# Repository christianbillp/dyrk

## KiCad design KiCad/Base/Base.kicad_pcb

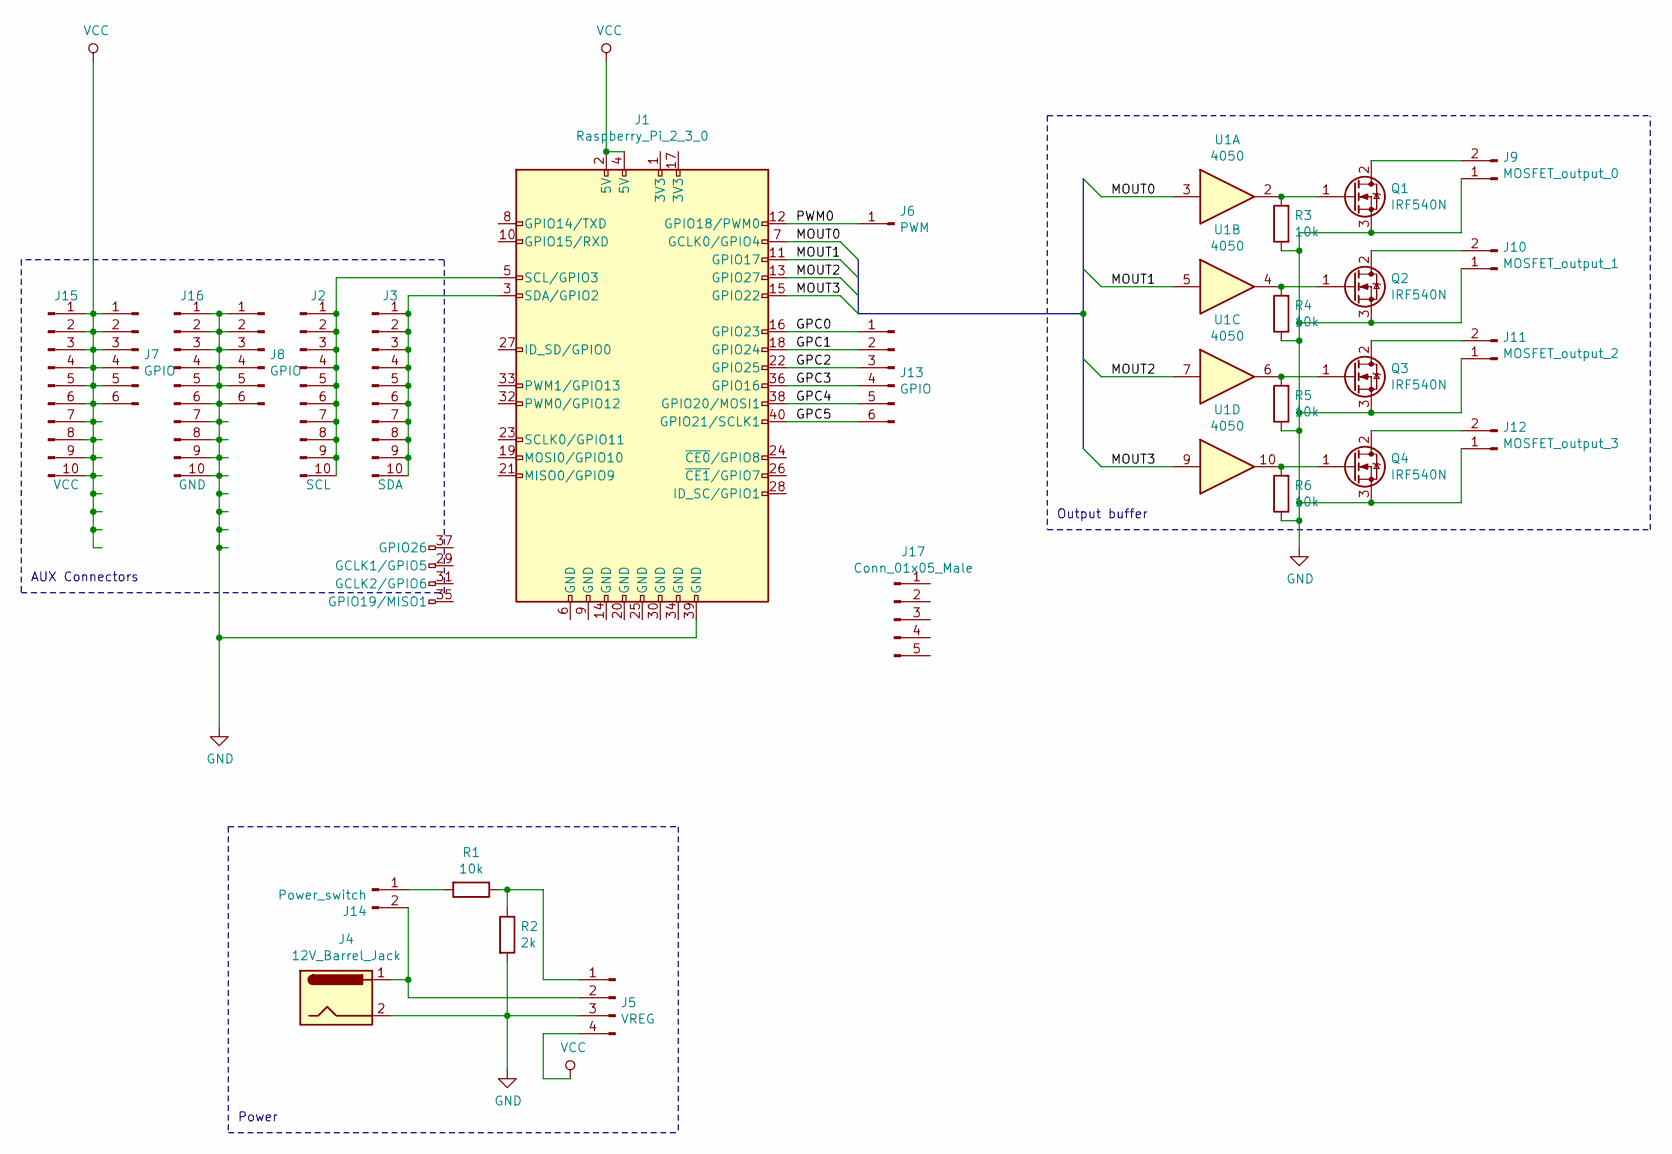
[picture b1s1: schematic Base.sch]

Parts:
J1: Raspberry_Pi_2_3_0; PinHeader_2x20_P2.54mm_Vertical
J2: SCL; PinHeader_1x10_P2.54mm_Vertical
J3: SDA; PinHeader_1x10_P2.54mm_Vertical
J4: 12V_Barrel_Jack; BarrelJack_Horizontal
J5: VREG; PinHeader_1x04_P2.54mm_Vertical
J6: PWM; PinHeader_1x01_P2.54mm_Vertical
J7, J8, J13: GPIO; PinHeader_1x06_P2.54mm_Vertical
J9: MOSFET_output_0; PinHeader_1x02_P2.54mm_Vertical
J10: MOSFET_output_1; PinHeader_1x02_P2.54mm_Vertical
J11: MOSFET_output_2; PinHeader_1x02_P2.54mm_Vertical
J12: MOSFET_output_3; PinHeader_1x02_P2.54mm_Vertical
J14: Power_switch; PinHeader_1x02_P2.54mm_Vertical
J15: VCC; PinHeader_1x10_P2.54mm_Vertical
J16: GND; PinHeader_1x10_P2.54mm_Vertical
J17: Conn_01x05_Male
Q1, Q2, Q3, Q4: IRF540N; TO-220-3_Vertical
R1, R3, R4, R5, R6: 10k; R_Axial_DIN0207_L6.3mm_D2.5mm_P10.16mm_Horizontal
R2: 2k; R_Axial_DIN0207_L6.3mm_D2.5mm_P10.16mm_Horizontal
U1: 4050; DIP-16_W7.62mm_Socket

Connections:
/GPC0: J1.16 (GPIO23), J13.1
/GPC1: J1.18 (GPIO24), J13.2
/GPC2: J1.22 (GPIO25), J13.3
/GPC3: J1.36 (GPIO16), J13.4
/GPC4: J1.38 (GPIO20/MOSI1), J13.5
/GPC5: J1.40 (GPIO21/SCLK1), J13.6
/MOUT0: J1.7 (GCLK0/GPIO4), U1.3
/MOUT1: J1.11 (GPIO17), U1.5
/MOUT2: J1.13 (GPIO27), U1.7
/MOUT3: J1.15 (GPIO22), U1.9
/PWM0: J1.12 (GPIO18/PWM0), J6.1
GND: J1.39 (GND), J4.2, J5.3, J8.1, J8.2, J8.3, J8.4, J8.5, J8.6, J9.1, J10.1, J11.1, J12.1, J16.1, J16.2, J16.3, J16.4, J16.5, J16.6, J16.7, J16.8, J16.9, J16.10, Q1.3 (S), Q2.3 (S), Q3.3 (S), Q4.3 (S), R2.2, R3.1, R4.1, R5.1, R6.1
unnamed: J1.3 (SDA/GPIO2), J3.1, J3.2, J3.3, J3.4, J3.5, J3.6, J3.7, J3.8, J3.9, J3.10
unnamed: J1.5 (SCL/GPIO3), J2.1, J2.2, J2.3, J2.4, J2.5, J2.6, J2.7, J2.8, J2.9, J2.10
unnamed: J5.1, R1.1, R2.1
unnamed: J9.2, Q1.2 (D)
unnamed: J10.2, Q2.2 (D)
unnamed: J11.2, Q3.2 (D)
unnamed: J12.2, Q4.2 (D)
unnamed: J14.1, R1.2
unnamed: J4.1, J5.2, J14.2
unnamed: Q1.1 (G), R3.2, U1.2
unnamed: Q2.1 (G), R4.2, U1.4
unnamed: Q3.1 (G), R5.2, U1.6
unnamed: Q4.1 (G), R6.2, U1.10
VCC: J1.2 (5V), J1.4 (5V), J5.4, J7.1, J7.2, J7.3, J7.4, J7.5, J7.6, J15.1, J15.2, J15.3, J15.4, J15.5, J15.6, J15.7, J15.8, J15.9, J15.10

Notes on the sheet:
Output buffer
Power
AUX Connectors

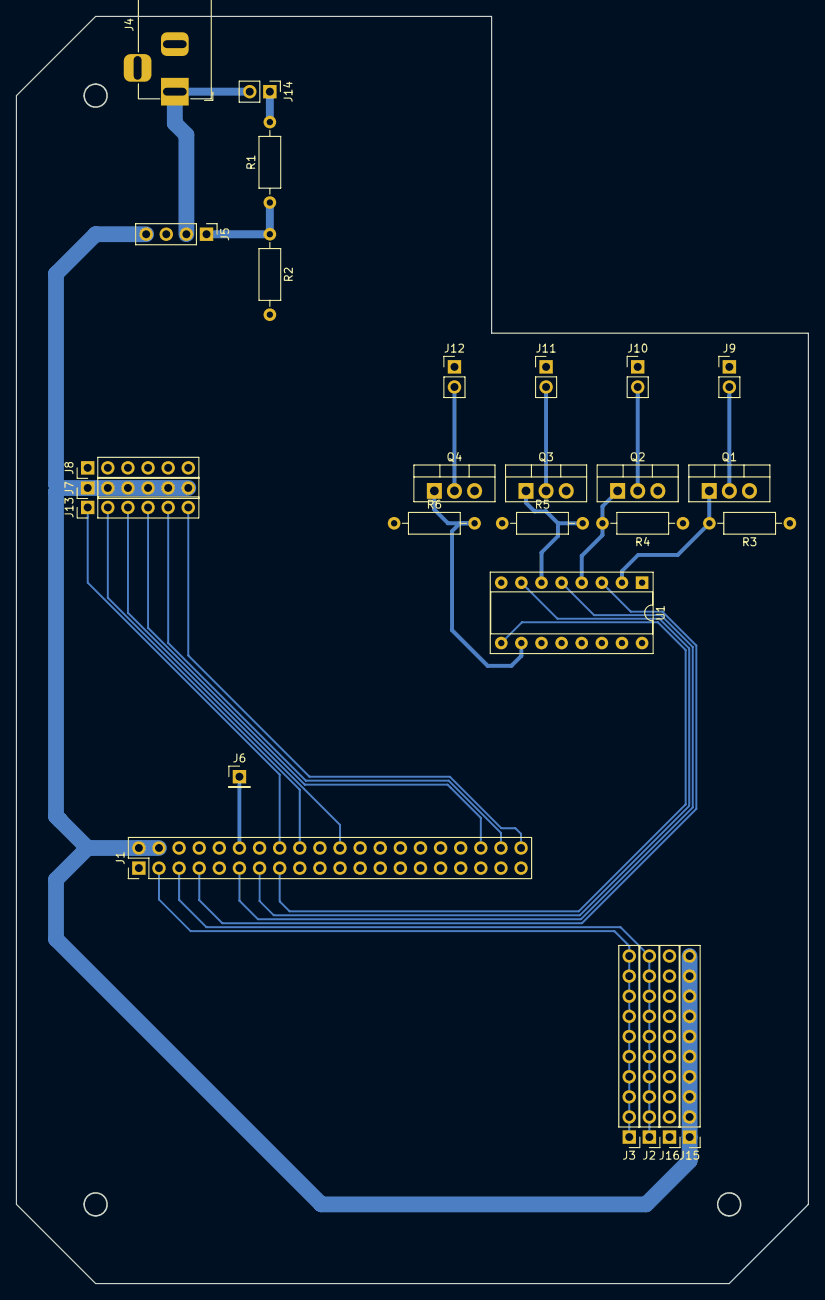
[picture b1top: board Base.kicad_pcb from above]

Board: 2 copper layers, 100.0 x 159.9 mm, 27 parts (0 on the bottom side), 26 nets.

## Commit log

2018-11-20 First working sample. Running on prototype 1
2018-11-21 Example visualizations in main.py
2018-11-24 Working prototype controller
2018-11-24 Base board draft 1
2018-12-01 Added pull-down resistors to MOSFET outputs
2018-12-08 Added configurator. Tested base_controller in base_board
